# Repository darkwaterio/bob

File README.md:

#Bob the AUV

This repository contains the hardware and firmware files for the Bob Float.

Verisons contained in this repository

##Mk1

This version was built for demonstration at the Big Bang Fair 2015 and is the first deployment of Bob. There are quite a few niggles to be fixed and updates that are planned for Bob based on the findings from this version, so it's not recommended that you spend much time with it - however, there will be a lot of cross-over of parts with the next version so you wouldn't need to rebuild everything for Mk2

Mk1 can be found at https://github.com/darkwaterfoundation/bob/tree/mk1

##Mk2

This version had a few improvements to the code and bottom cap designs to attempt to fix a small leak discovered in the Mk1. This version was shown at Maker Faire UK and the Dublin Maker events

Mk2 can be found at https://github.com/darkwaterfoundation/bob/tree/mk2

##Development

The development branch contains the ongoing designs and work on Mk3 - This is a dramatic redesign and simplifcation. We've moved from using the Spark / Particle core / photon microcontrollers to a dual Arduino Pro Mini system and from Wifi to a longer range wireless communication system.

The Development version can be found at https://github.com/darkwaterfoundation/bob/tree/development

##Repositories Layout

- hardware - contains three directories
  - stl contains the 3D printed parts files
  - svg contains the laser cutting files - you may need to alter the outside widths of circles based on the kerf of your cutter
  - pcb contains the eagle files for the required PCBs.
- firmware - contains the firmware for the particular version of Bob - Mk1 and Mk2 use Spark / Particle processors, Future versions are Arduino.

##Preliminary Bill of Materials

https://docs.google.com/spreadsheets/d/1KixPCNF-eNdthVP5A6QqYoAs1JIhs3zF5F2K2lznduw/edit?usp=sharing

##Build instructions

Will be up soon

##License

This work is licensed under the Creative Commons Attribution-NonCommercial-ShareAlike 4.0 International License. To view a copy of this license, visit http://creativecommons.org/licenses/by-nc-sa/4.0/ or send a letter to Creative Commons, 444 Castro Street, Suite 900, Mountain View, California, 94041, USA.

*Some portions of code may be subject to different licensing agreements.

THE SOFTWARE IS PROVIDED “AS IS”, WITHOUT WARRANTY OF ANY KIND, EXPRESS OR IMPLIED, INCLUDING BUT NOT LIMITED TO THE WARRANTIES OF MERCHANTABILITY, FITNESS FOR A PARTICULAR PURPOSE AND NONINFRINGEMENT. IN NO EVENT SHALL THE AUTHORS OR COPYRIGHT HOLDERS BE LIABLE FOR ANY CLAIM, DAMAGES OR OTHER LIABILITY, WHETHER IN AN ACTION OF CONTRACT, TORT OR OTHERWISE, ARISING FROM, OUT OF OR IN CONNECTION WITH THE SOFTWARE OR THE USE OR OTHER DEALINGS IN THE SOFTWARE.

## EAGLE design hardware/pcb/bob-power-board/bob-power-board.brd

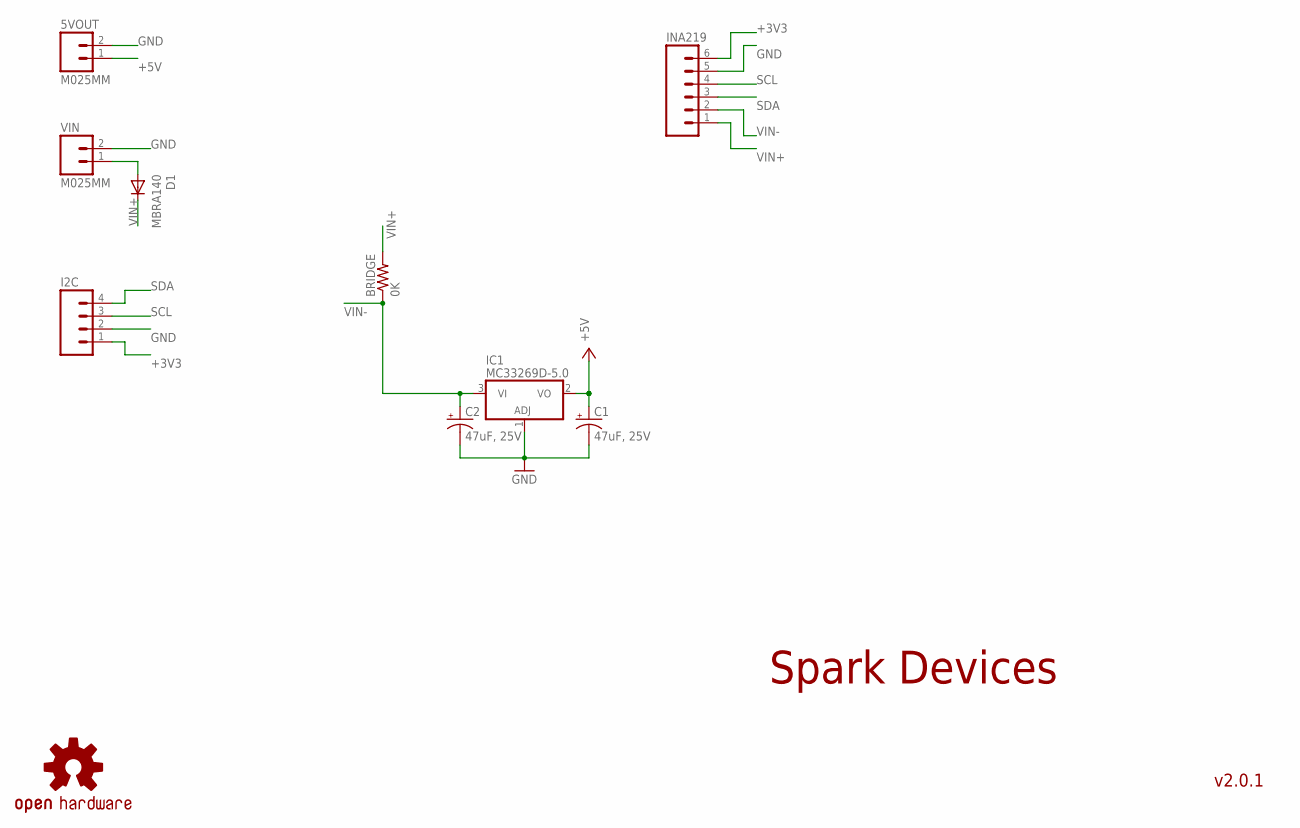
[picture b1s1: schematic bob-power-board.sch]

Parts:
5VOUT: M025MM; SCREWTERMINAL-5MM-2
BRIDGE: 0K; 1206
C1, C2: 47uF, 25V; CPOL-RADIAL-100UF-25V
D1: MBRA140; SMA-DIODE
I2C: M04LOCK; 1X04_LOCK
IC1: MC33269D-5.0; DPACK
INA219: M06LOCK; 1X06_LOCK
LOGO1: OSHW-LOGOM; OSHW-LOGO-M
VIN: M025MM; SCREWTERMINAL-5MM-2

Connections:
+3V3: I2C.1, INA219.6
+5V: 5VOUT.1, C1.1 (+), IC1.2 (VO)
GND: 5VOUT.2, C1.2 (-), C2.2 (-), I2C.2, IC1.1 (ADJ), INA219.5, VIN.2
unnamed: D1.A, VIN.1
SCL: I2C.3, INA219.4
SDA: I2C.4, INA219.3
VIN+: BRIDGE.2, D1.C, INA219.1
VIN-: BRIDGE.1, C2.1 (+), IC1.3 (VI), INA219.2

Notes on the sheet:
Spark Devices
v2.0.1

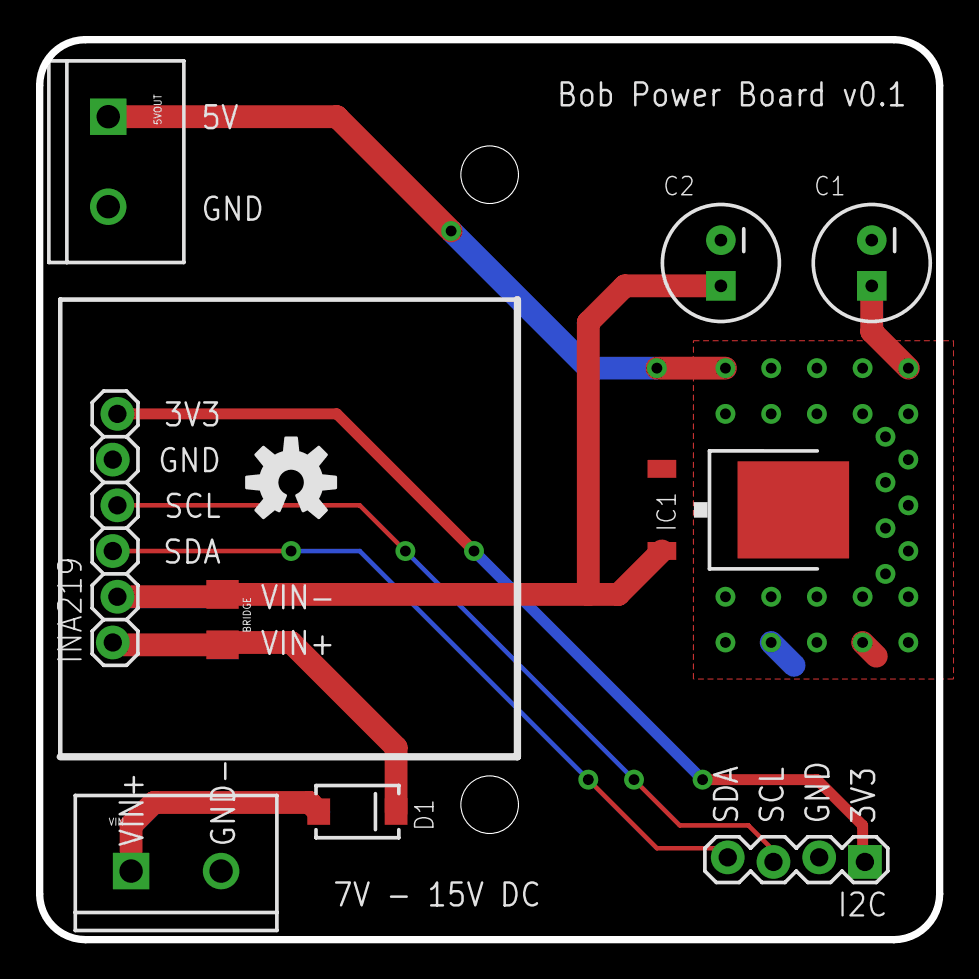
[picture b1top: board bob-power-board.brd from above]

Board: 2 copper layers, 50.0 x 50.0 mm, 10 parts (0 on the bottom side), 8 nets.

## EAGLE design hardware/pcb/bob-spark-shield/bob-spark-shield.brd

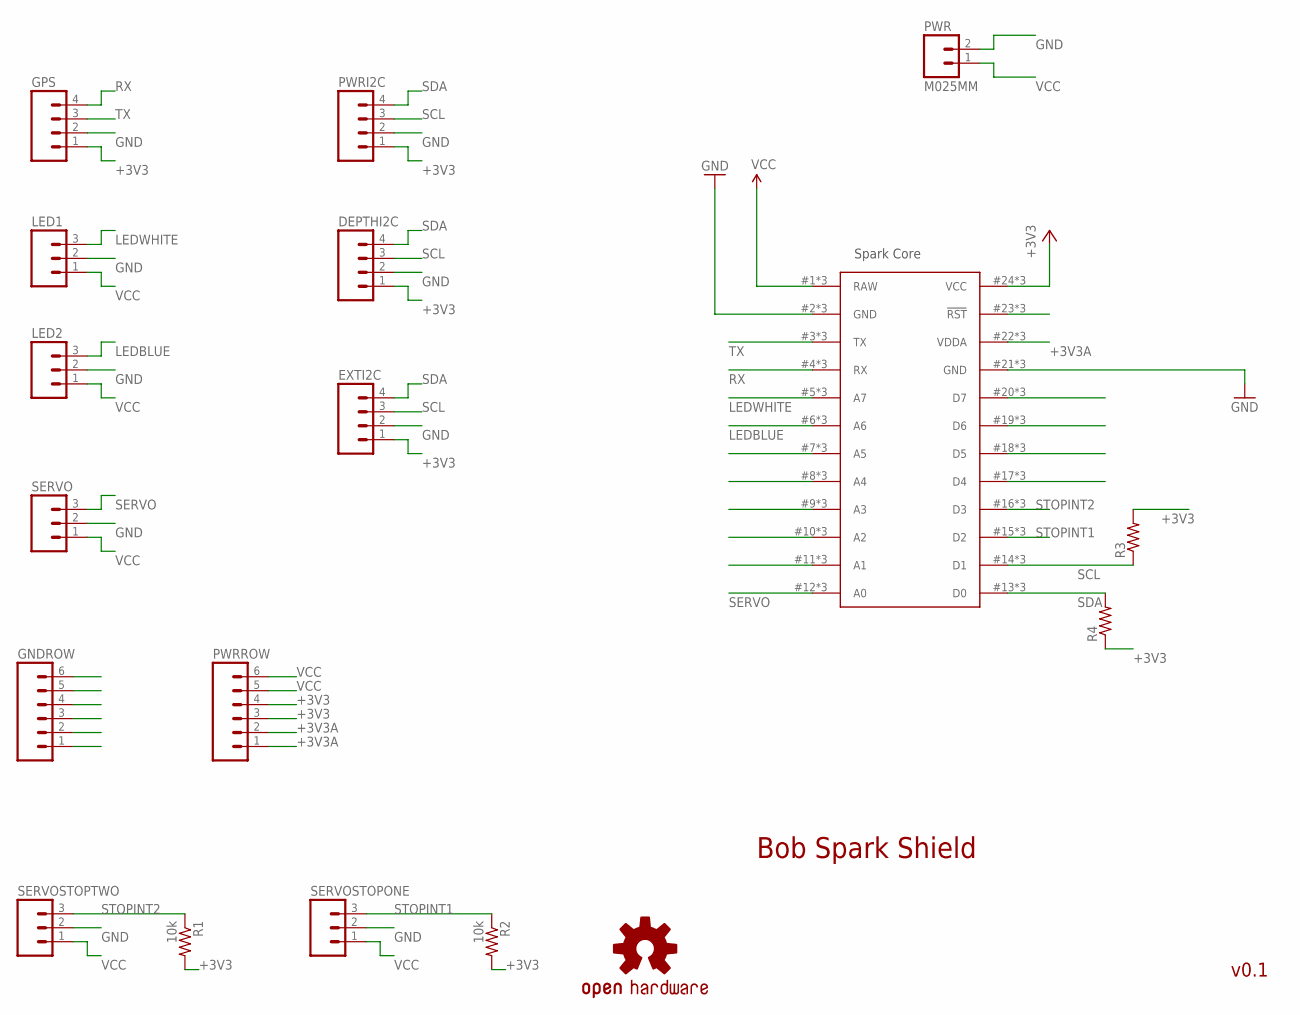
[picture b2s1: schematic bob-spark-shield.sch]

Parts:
DEPTHI2C: M04LOCK; 1X04_LOCK
EXTI2C: M04LOCK; 1X04_LOCK
GNDROW: M06LOCK; 1X06_LOCK
GPS: M04LOCK; 1X04_LOCK
LED1, LED2: M03LOCK; 1X03_LOCK
LOGO1: OSHW-LOGOM; OSHW-LOGO-M
PWR: M025MM; SCREWTERMINAL-5MM-2
PWRI2C: M04LOCK; 1X04_LOCK
PWRROW: M06LOCK; 1X06_LOCK
R1, R2: 10k; 0805
R3, R4: RESISTOR0805-RES; 0805
SERVO: M03LOCK; 1X03_LOCK
SERVOSTOPONE: M03LOCK; 1X03_LOCK
SERVOSTOPTWO: M03LOCK; 1X03_LOCK
U$1: SPARK_CORE; SPARK_CORE_STACKABLE

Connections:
+3V3: DEPTHI2C.1, EXTI2C.1, GPS.1, PWRI2C.1, PWRROW.3, PWRROW.4, R1.2, R2.2, R3.2, R4.1, U$1.24 (VCC), U$1.#24 (VCC), U$1.@24 (VCC)
+3V3A: PWRROW.1, PWRROW.2, U$1.22 (VDDA), U$1.#22 (VDDA), U$1.@22 (VDDA)
GND: DEPTHI2C.2, EXTI2C.2, GNDROW.1, GNDROW.2, GNDROW.3, GNDROW.4, GNDROW.5, GNDROW.6, GPS.2, LED1.2, LED2.2, PWR.2, PWRI2C.2, SERVO.2, SERVOSTOPONE.2, SERVOSTOPTWO.2, U$1.2 (GND), U$1.21 (GND), U$1.#2 (GND), U$1.#21 (GND), U$1.@2 (GND), U$1.@21 (GND)
LEDBLUE: LED2.3, U$1.6 (A6), U$1.#6 (A6), U$1.@6 (A6)
LEDWHITE: LED1.3, U$1.5 (A7), U$1.#5 (A7), U$1.@5 (A7)
unnamed: U$1.11 (A1), U$1.#11 (A1), U$1.@11 (A1)
unnamed: U$1.10 (A2), U$1.#10 (A2), U$1.@10 (A2)
unnamed: U$1.9 (A3), U$1.#9 (A3), U$1.@9 (A3)
unnamed: U$1.8 (A4), U$1.#8 (A4), U$1.@8 (A4)
unnamed: U$1.7 (A5), U$1.#7 (A5), U$1.@7 (A5)
unnamed: U$1.18 (D5), U$1.#18 (D5), U$1.@18 (D5)
unnamed: U$1.17 (D4), U$1.#17 (D4), U$1.@17 (D4)
unnamed: U$1.19 (D6), U$1.#19 (D6), U$1.@19 (D6)
unnamed: U$1.20 (D7), U$1.#20 (D7), U$1.@20 (D7)
unnamed: U$1.23 (!RST), U$1.#23 (!RST), U$1.@23 (!RST)
RX: GPS.4, U$1.4 (RX), U$1.#4 (RX), U$1.@4 (RX)
SCL: DEPTHI2C.3, EXTI2C.3, PWRI2C.3, R3.1, U$1.14 (D1), U$1.#14 (D1), U$1.@14 (D1)
SDA: DEPTHI2C.4, EXTI2C.4, PWRI2C.4, R4.2, U$1.13 (D0), U$1.#13 (D0), U$1.@13 (D0)
SERVO: SERVO.3, U$1.12 (A0), U$1.#12 (A0), U$1.@12 (A0)
STOPINT1: R2.1, SERVOSTOPONE.3, U$1.15 (D2), U$1.#15 (D2), U$1.@15 (D2)
STOPINT2: R1.1, SERVOSTOPTWO.3, U$1.16 (D3), U$1.#16 (D3), U$1.@16 (D3)
TX: GPS.3, U$1.3 (TX), U$1.#3 (TX), U$1.@3 (TX)
VCC: LED1.1, LED2.1, PWR.1, PWRROW.5, PWRROW.6, SERVO.1, SERVOSTOPONE.1, SERVOSTOPTWO.1, U$1.1 (RAW), U$1.#1 (RAW), U$1.@1 (RAW)

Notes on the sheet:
Spark Core
Bob Spark Shield
v0.1

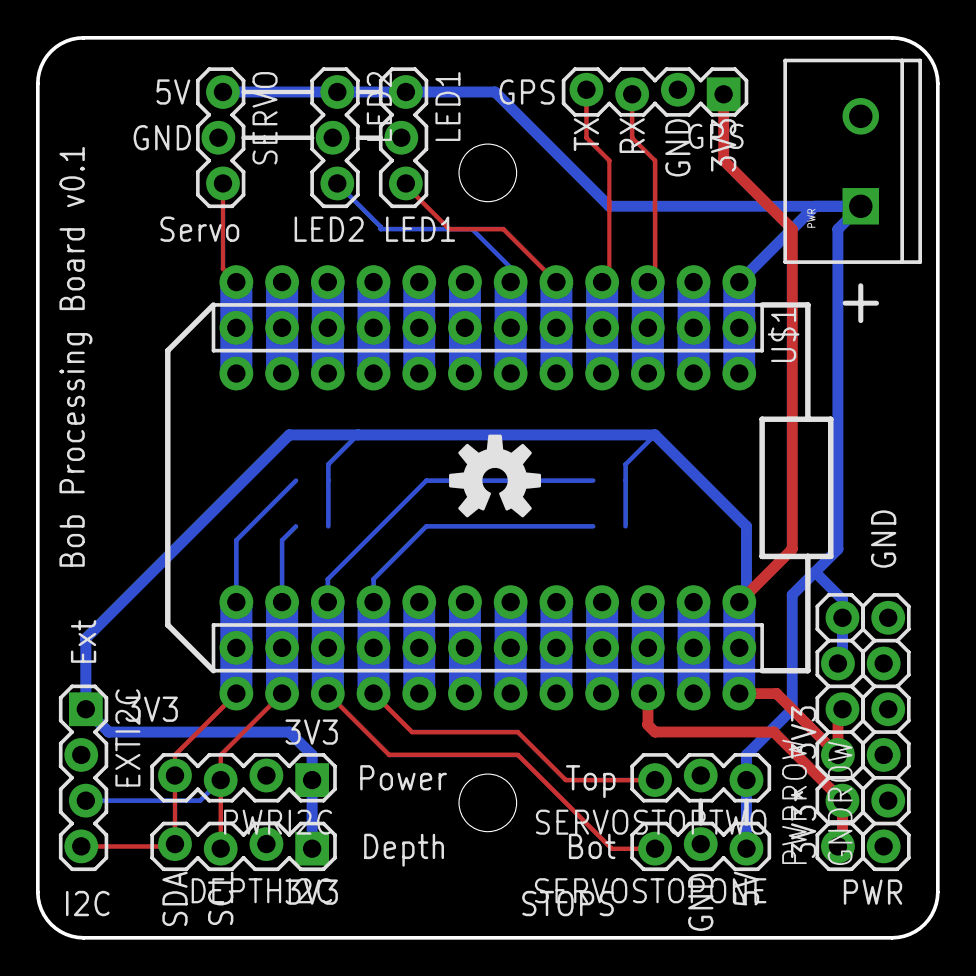
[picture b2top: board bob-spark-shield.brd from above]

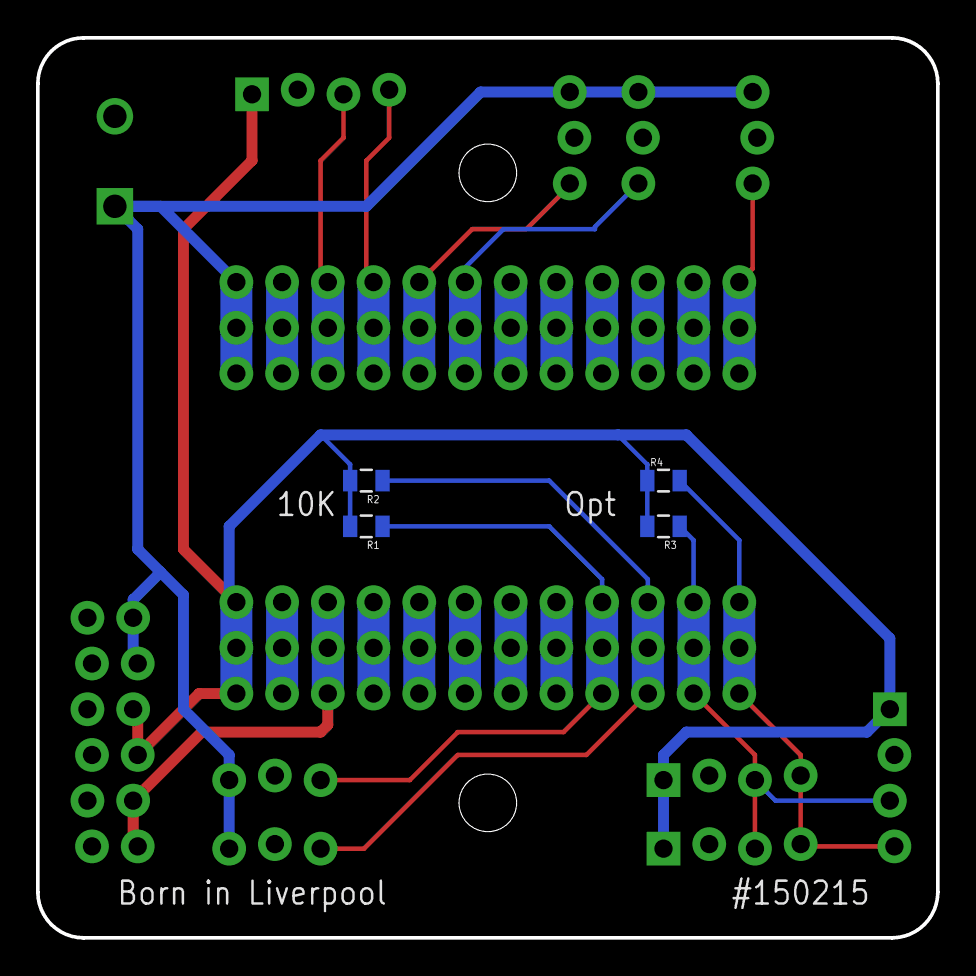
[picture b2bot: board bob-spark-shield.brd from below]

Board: 2 copper layers, 50.0 x 50.0 mm, 18 parts (4 on the bottom side), 23 nets.

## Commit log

2014-12-16 Added initial STP files
2014-12-16 Added initial 3D printing STL
2014-12-16 Updated read me
2014-12-16 Add extra directories
2015-03-20 change directory format to new layout
2015-03-20 updated reame for new structure
2015-03-20 Added PCB files
    Added the eagle files for the processor board and power board
2015-03-20 Added demonstration firmware
2015-03-20 oops grammar
2015-03-20 ditto
2015-03-20 Initial STL files
2015-03-20 re-orient some parts for better printing
2015-03-20 Quick update
2015-03-20 Added 5mm and 3mm cutting files
    Needs multiples of some pieces, just put one of each on the files.
2015-03-20 Added license
2015-06-03 linked to mk2
2015-09-07 Change mk2 link
2015-09-07 pulled mk1 designs
2015-09-08 Top cap laser files and dome mount
2015-09-08 remove files from master
2015-09-08 bottom cap laser cut pieces
2015-09-08 Added end cap brace
2015-09-16 updated cap designs
    new cap designs
    more files formats
    added laser directory for "LaserCut" software format

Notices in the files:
parts and their libraries:
SparkFun-Capacitors: Licensing: CC v3.0 Share-Alike You are welcome to use this library for commercial purposes.
SparkFun-Resistors: Licensing: Creative Commons ShareAlike 4.0 International - https://creativecommons.org/licenses/by-sa/4.0
